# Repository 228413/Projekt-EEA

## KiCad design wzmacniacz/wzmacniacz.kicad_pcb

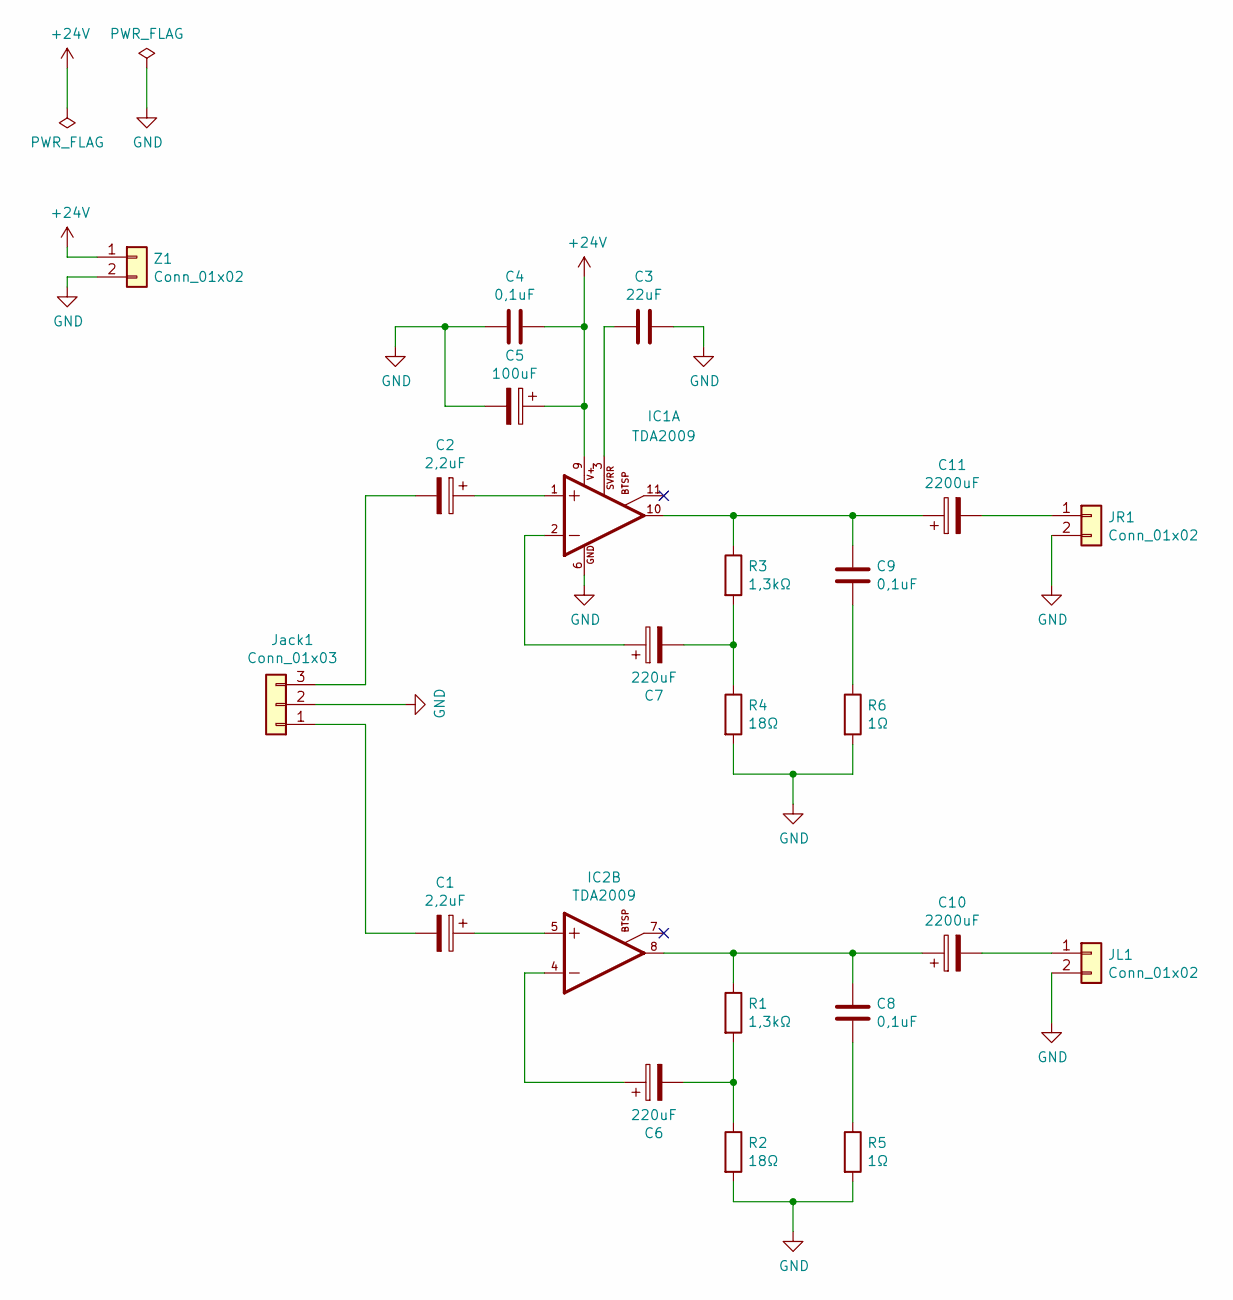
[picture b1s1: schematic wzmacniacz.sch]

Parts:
C1, C2: 2,2uF; CP_Radial_D5.0mm_P2.00mm
C3: 22uF; CP_Radial_D6.3mm_P2.50mm
C4, C8, C9: 0,1uF; C_Disc_D4.7mm_W2.5mm_P5.00mm
C5: 100uF; C_Radial_D12.5mm_H20.0mm_P5.00mm
C6, C7: 220uF; C_Radial_D12.5mm_H25.0mm_P5.00mm
C10, C11: 2200uF; C_Radial_D18.0mm_H35.5mm_P7.50mm
IC1, IC2: TDA2009; SIP11
JL1: Conn_01x02; TerminalBlock_Phoenix_MKDS-1,5-2_1x02_P5.00mm_Horizontal
JR1: Conn_01x02; TerminalBlock_Phoenix_MKDS-1,5-2_1x02_P5.00mm_Horizontal
Jack1: Conn_01x03; TerminalBlock_Phoenix_MKDS-1,5-3-5.08_1x03_P5.08mm_Horizont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
R1, R3: 1,3kΩ; R_Axial_DIN0309_L9.0mm_D3.2mm_P12.70mm_Horizontal
R2, R4: 18Ω; R_Axial_DIN0309_L9.0mm_D3.2mm_P12.70mm_Horizontal
R5, R6: 1Ω; R_Axial_DIN0309_L9.0mm_D3.2mm_P12.70mm_Horizontal
Z1: Conn_01x02; TerminalBlock_Phoenix_MKDS-1,5-2_1x02_P5.00mm_Horizontal

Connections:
+24V: C4.1, C5.1, IC1.9, Z1.1
GND: C3.1, C4.2, C5.2, IC1.6, JL1.2, JR1.2, Jack1.2, R2.2, R4.2, R5.2, R6.2, Z1.2
unnamed: C1.1, IC2.5
unnamed: C1.2, Jack1.1
unnamed: C2.1, IC1.1
unnamed: C2.2, Jack1.3
unnamed: C3.2, IC1.3
unnamed: C6.1, IC2.4
unnamed: C6.2, R1.2, R2.1
unnamed: C7.1, IC1.2
unnamed: C7.2, R3.2, R4.1
unnamed: C8.2, R5.1
unnamed: C9.2, R6.1
unnamed: C8.1, C10.1, IC2.8, R1.1
unnamed: C10.2, JL1.1
unnamed: C9.1, C11.1, IC1.10, R3.1
unnamed: C11.2, JR1.1

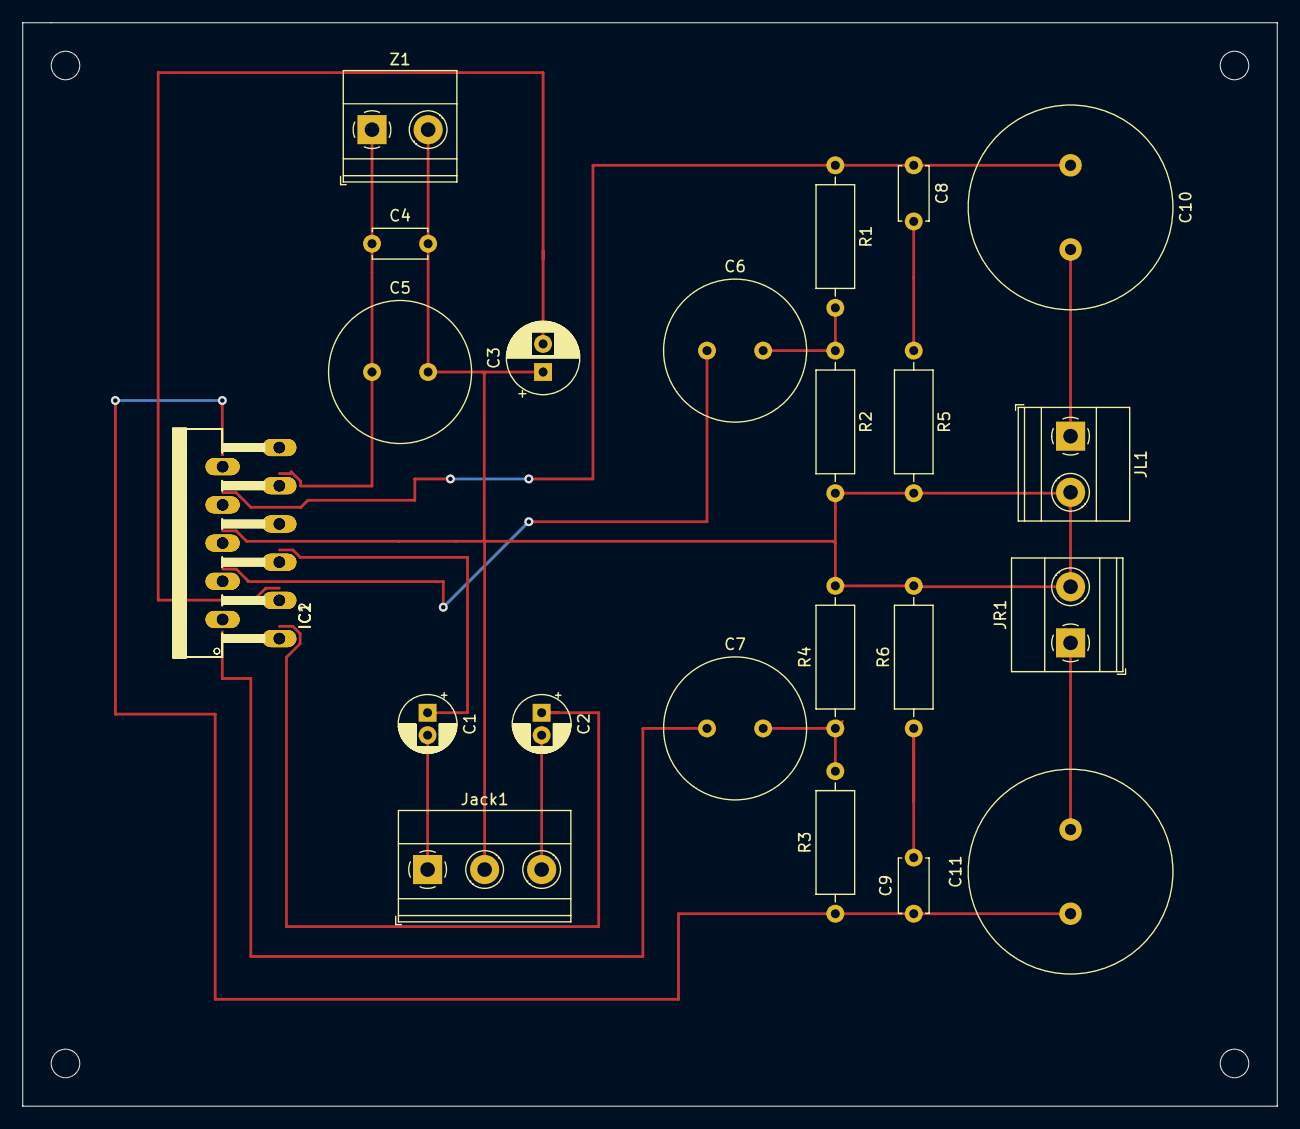
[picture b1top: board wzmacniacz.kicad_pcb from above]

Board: 2 copper layers, 111.8 x 96.5 mm, 23 parts (0 on the bottom side), 17 nets.

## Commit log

2022-01-20 schemat
2022-01-20 Złącza Z1 i JL1 są zaprojektowane odwrotnie, dla wygody prowadzenia ścierzek, ale elementy będą przylutowane we własciwy sposób
2022-01-20 Zielone ścieżki na schemacie to zworki
2022-01-20 Deleted the files form repo
2022-01-20 Złącza Z1 i JL1 sa na schemacie odwrotnie niż będą zamontowane, ponieważ ułatwiło to poprowadzenie ścieżek. Przylutowane będą we właściwy sposób
2022-01-20 Footprint układu TDA2009 znaleziony w internecie i zaimportowany do KiCada
2022-01-20 Schemat układu w programie Tina
2022-01-20 Różne wersje układu płytki PCB w pogramie KiCad powstałe podczas projektowania. Finalna wersja nazwę wzmacniacz.[rozszerzenie] (nie posiada numeru)
2022-01-20 Skład grupy,godzina zajęć
2022-02-09 Sprawozdanie końcowe z projektu
